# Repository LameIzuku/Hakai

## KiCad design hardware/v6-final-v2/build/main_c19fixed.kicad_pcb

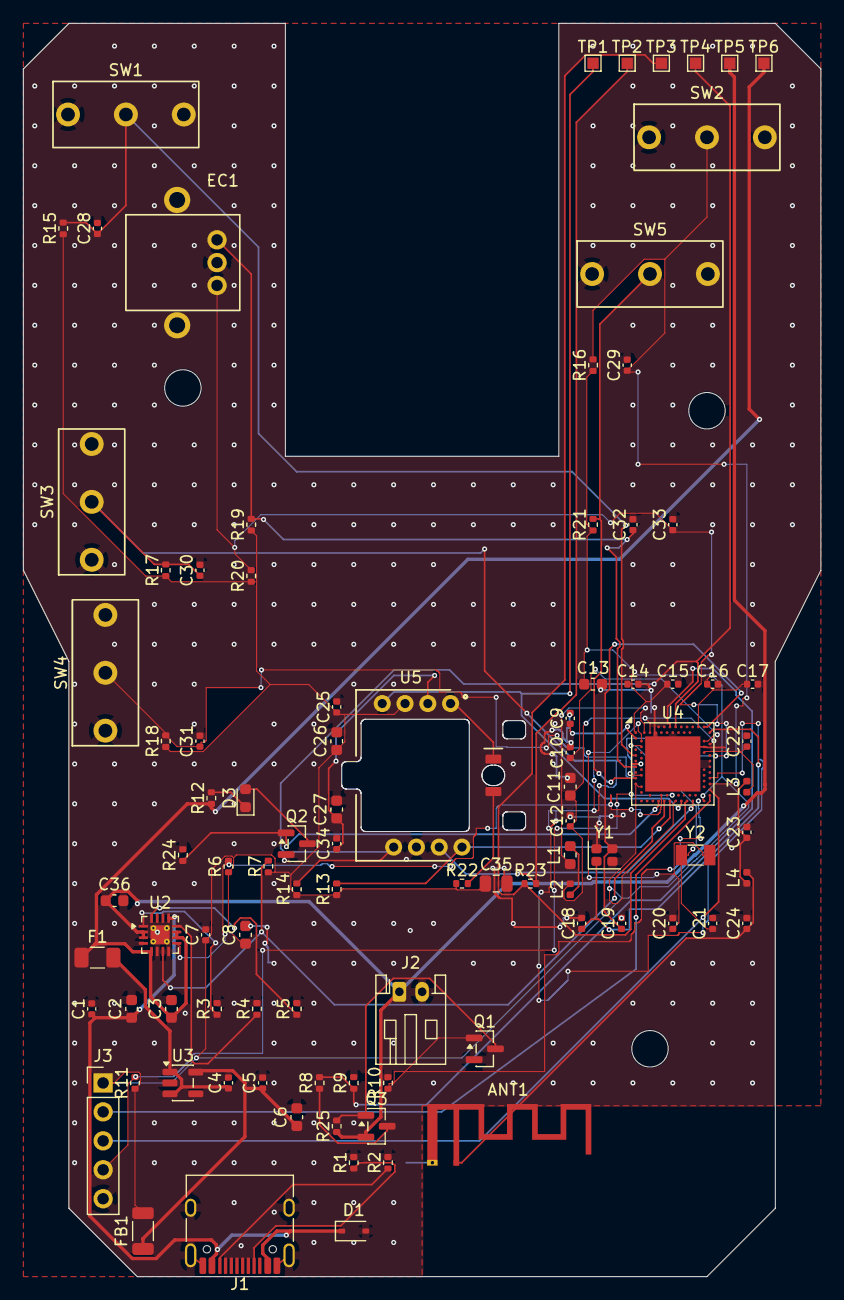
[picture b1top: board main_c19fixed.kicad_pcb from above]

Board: 2 copper layers, 70.0 x 110.0 mm, 98 parts (0 on the bottom side), 51 nets.

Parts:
ANT1: PCB IFA 2.4GHz; Texas_SWRA117D_2.4GHz_Right
C1, C4, C5, C14: 1uF; C_0402_1005Metric
C2, C3, C6, C8, C26, C36: 10uF; C_0603_1608Metric
C7, C9, C15, C16, C17, C25, C34: 100nF; C_0402_1005Metric
C10: 100pF NP0; C_0402_1005Metric
C11: 1uF; C_0603_1608Metric
C12: 47nF; C_0402_1005Metric
C13: 4.7uF; C_0603_1608Metric
C18, C19, C20, C21: 12pF NP0; C_0402_1005Metric
C22: 1.0pF NP0; C_0402_1005Metric
C23: 1.2pF NP0; C_0402_1005Metric
C24: 1.2pF (DNP); C_0402_1005Metric
C27: 4.7uF/10V; C_0603_1608Metric
C28, C29, C30, C31: 100nF (DNP); C_0402_1005Metric
C32, C33: 10nF; C_0402_1005Metric
C35: 33uF; C_0805_2012Metric
D1: PESD5V0S1BA; D_SOD-323
D2: IR LED (SMT / L0AJ-LSG1 set); IRLED_L0AJ_3311
D3: BLUE; LED_0603_1608Metric
EC1: 11mm encoder; ENC_Mouse_11mm
F1: PTC 1A; Fuse_1206_3216Metric
FB1: 600R@100MHz; L_1206_3216Metric
J1: USB4105-GF-A; USB_C_Receptacle_HRO_TYPE-C-31-M-12
J2: JST S2B-PH-K; JST_PH_S2B-PH-K_1x02_P2.00mm_Horizontal
J3: SWD 1x05; PinHeader_1x05_P2.54mm_Vertical
L1: 10uH; L_0603_1608Metric
L2: 15nH; L_0402_1005Metric
L3: 4.7nH; L_0402_1005Metric
L4: 2.2nH; L_0402_1005Metric
MH1, MH2, MH3: M3; MountingHole_3.2mm_M3
Q1, Q2: AO3400A; SOT-23
Q3: AO3401A; SOT-23
R1, R2: 5.1k; R_0402_1005Metric
R3, R11, R13, R15, R16, R17, R18, R19, R20, R21: 10k; R_0402_1005Metric
R4: 3.24k; R_0402_1005Metric
R5: 2.0k; R_0402_1005Metric
R6, R7, R9, R10, R24: 100k; R_0402_1005Metric
R8: 200k; R_0402_1005Metric
R12: 1k; R_0402_1005Metric
R14: 10k (DNP); R_0402_1005Metric
R22: 18R 1%; R_0402_1005Metric
R23: 3.3k 1%; R_0402_1005Metric
R25: 47k; R_0402_1005Metric
SW1, SW2, SW3, SW4, SW5: Kailh GM 8.0; SW_Kailh_GM8_D2F
TP1: TP1; TestPoint_Pad_1.0x1.0mm
TP2: TP2; TestPoint_Pad_1.0x1.0mm
TP3: TP3; TestPoint_Pad_1.0x1.0mm
TP4: TP4; TestPoint_Pad_1.0x1.0mm
TP5: TP5; TestPoint_Pad_1.0x1.0mm
TP6: TP6; TestPoint_Pad_1.0x1.0mm
U2: BQ24074; VQFN-16-1EP_3x3mm_P0.5mm_EP1.68x1.68mm_ThermalVias
U3: XC6219B192MR; SOT-23-5
U4: nRF52833-QIAA (Bxx+); Nordic_AQFN-73-1EP_7x7mm_P0.5mm
U5: PAW3311DB-T2MU; PAW3311DB_iDIP8_L0AJ
Y1: 32MHz CL=8pF; Crystal_SMD_2016-4Pin_2.0x1.6mm
Y2: 32.768kHz CL=9pF; Crystal_SMD_3215-2Pin_3.2x1.5mm

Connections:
1V9: C5.1, C6.1, FB1.1, U3.5
1V9_A: C7.1, C8.1, C13.1, C14.1, C15.1, C16.1, C17.1, C25.1, C26.1, C35.1, FB1.2, J3.1, R6.1, R7.1, R11.1, R13.1, R14.1, R15.1, R16.1, R17.1, R18.1, R19.1, R20.1, R21.1, R22.1, U4.A22, U4.AD14, U4.AD23, U4.B1, U4.W1, U4.Y2, U5.3
ANT: C22.1, L3.1, U4.H23
BTN_LEFT: C28.1, R15.2, SW1.2, U4.J1
BTN_RIGHT: C29.1, R16.2, SW2.2, U4.W24
BTN_SIDE_BACK: C30.1, R17.2, SW3.2, U4.U24
BTN_SIDE_FWD: C31.1, R18.2, SW4.2, U4.M2
CC1: J1.A5, R1.1
CC2: J1.B5, R2.1
DCC: L1.1, U4.B3
DCC_L: L1.2, L2.1
DEC1: C9.1, U4.C1
DEC3: C10.1, U4.D23
DEC4_6: C11.1, C12.1, L2.2, U4.B5, U4.E24
ENC_A: C32.1, EC1.A, R19.2, U4.N1
ENC_B: C33.1, EC1.B, R20.2, U4.T2
ENC_SW: R21.2, SW5.2, U4.U1
GND: ANT1.2, C1.2, C2.2, C3.2, C4.2, C5.2, C6.2, C7.2, C8.2, C9.2, C10.2, C11.2, C12.2, C13.2, C14.2, C15.2, C16.2, C17.2, C18.2, C19.2, C20.2, C21.2, C22.2, C23.2, C24.2, C25.2, C26.2, C27.2, C28.2, C29.2, C30.2, C31.2, C32.2, C33.2, C34.2, C35.2, C36.2, D1.2, EC1.C, J1.A1, J1.A12, J1.B1, J1.B12, J1.SH, J2.2, J3.5, Q1.2, Q2.2, R1.2, R2.2, R3.2, R4.2, R5.2, R9.2, R10.2, R24.2, SW1.1, SW2.1, SW3.1, SW4.1, SW5.1, U2.4, U2.6, U2.8, U2.17, U3.2, U4.B7, U4.EP, U4.F23, U5.6, Y1.2, Y1.4
ILIM: R4.1, U2.12
ISET: R5.1, U2.16
LDO_IN: C4.1, F1.2, U3.1, U3.3
LED_A: D3.1, R12.2
LED_DRV: D2.1, R22.2
LED_K: D3.2, Q2.3
LED_STAT: Q2.1, R24.1, U4.AD8
PGOOD: R7.2, U2.7, U4.AD10
RF1: C23.1, L3.2, L4.1
RF_FEED: ANT1.1, C24.1, L4.2
SENS_LED: D2.2, U5.1
SENS_MOTION: R14.2, TP4.1, U4.A14, U5.5
SENS_NCS: R13.2, U4.AD12, U5.8
SENS_SDIO: R23.2, TP2.1, U4.AD20, U5.7
SPI_MOSI: R23.1, TP3.1, U4.AD18
SPI_SCK: TP1.1, U4.AD16, U5.4
STAT: R6.2, U2.9, U4.AC9
SWDCLK: J3.3, U4.AA24
SWDIO: J3.2, U4.AC24
TS: R3.1, U2.1
VBAT: C36.1, J2.1, Q3.2, R25.1, TP5.1, U2.2, U2.3
VBAT_EN: Q1.1, R10.1, U4.AD22
VBAT_SENSE: R8.2, R9.1, U4.A12
VBAT_SW: Q3.3, R8.1
VBAT_SW_G: Q1.3, Q3.1, R25.2
VBUS: C1.1, C2.1, D1.1, J1.A4, J1.A9, J1.B4, J1.B9, U2.13
VDDREG: C27.1, C34.1, U5.2
VSYS: C3.1, F1.1, R12.1, TP6.1, U2.5, U2.10, U2.11
XC1: C18.1, U4.B24, Y1.1
XC2: C19.1, U4.A23, Y1.3
XL1: C20.1, U4.D2, Y2.1
XL2: C21.1, U4.F2, Y2.2
nRESET: J3.4, R11.2, U4.AC13
